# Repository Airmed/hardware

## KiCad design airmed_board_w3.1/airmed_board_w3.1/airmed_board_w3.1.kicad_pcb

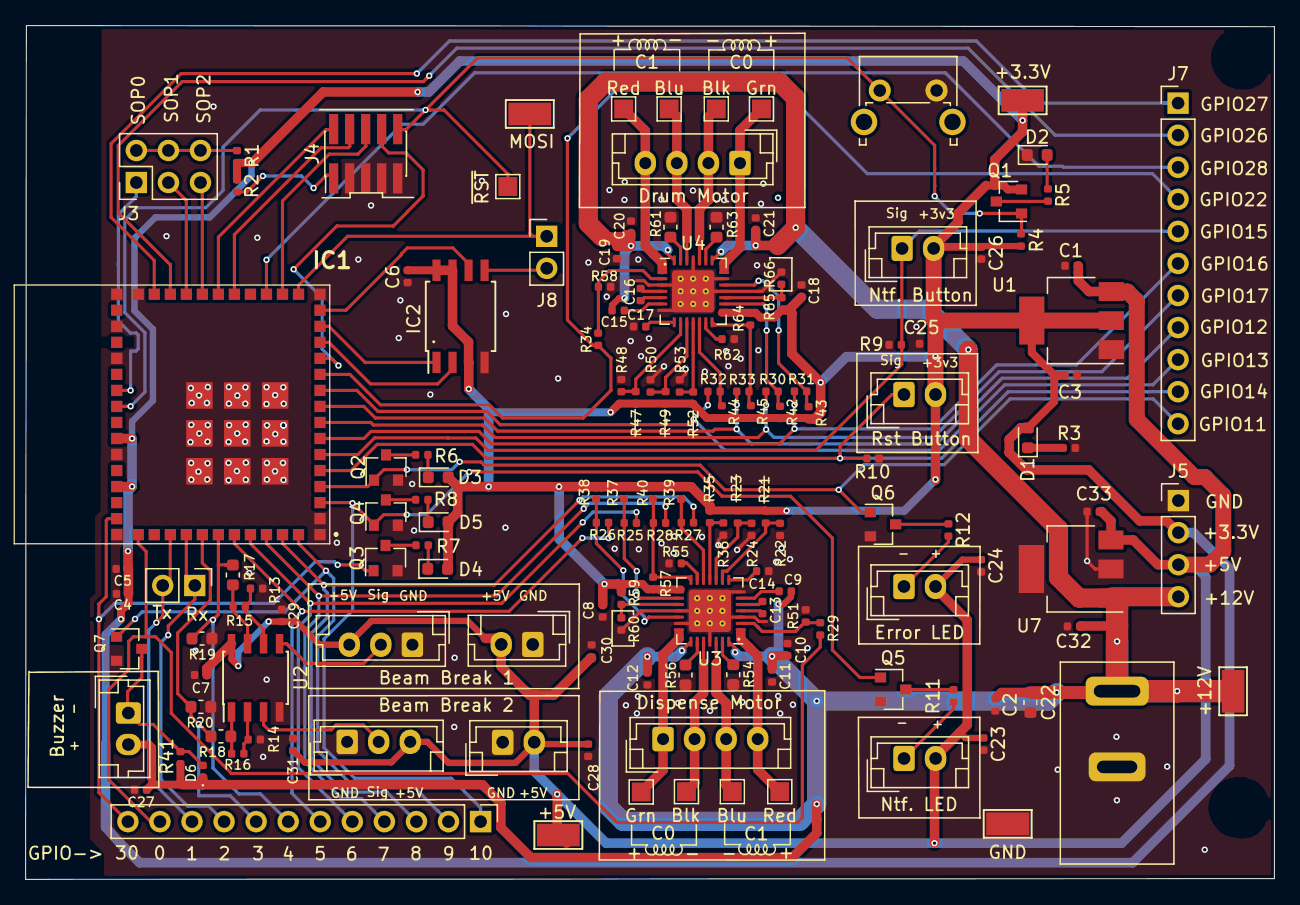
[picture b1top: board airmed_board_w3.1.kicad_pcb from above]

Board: 2 copper layers, 98.9 x 67.6 mm, 151 parts (0 on the bottom side), 102 nets.

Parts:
+3.3V, +5V, +12V: TestPoint_Flag; TestPoint_Keystone_5015_Micro-Minature
Blk: TestPoint_Flag; TestPoint_Pad_1.5x1.5mm
Blk#2: TestPoint_Flag; TestPoint_Pad_1.5x1.5mm
Blu: TestPoint_Flag; TestPoint_Pad_1.5x1.5mm
Blu#2: TestPoint_Flag; TestPoint_Pad_1.5x1.5mm
C1, C3, C10, C19: 4.7uF; C_0402_1005Metric
C2: 1uF; C_0402_1005Metric
C4, C5, C6, C7, C9, C11, C12, C13, C15, C16, C20, C21, C23, C24, C25, C26, C27, C28, C29, C30, C31, C33: 0.1uF; C_0402_1005Metric
C8, C14, C17, C18, C32: 0.22uF; C_0402_1005Metric
C22: 10uF; C_0603_1608Metric
D1, D2, D3, D4, D5: LED; LED_0603_1608Metric
D6: 350mV; D_0402_1005Metric
GND: TestPoint_Flag; TestPoint_Keystone_5015_Micro-Minature
Grn: TestPoint_Flag; TestPoint_Pad_1.5x1.5mm
Grn#2: TestPoint_Flag; TestPoint_Pad_1.5x1.5mm
IC1: CC3220MODASF12MONR; CC3220MODASM2MONR
IC2: MX25R3235FM1IL0; SOIJ-8_5.3x5.3mm_P1.27mm
J1, J8: Conn_01x02_Male; PinHeader_1x02_P2.54mm_Vertical
J2: Barrel_Jack; BarrelJack_CUI_PJ-037A_Horizontal
J3: Conn_02x03_Odd_Even; PinHeader_2x03_P2.54mm_Vertical
J4: Conn_02x05_Odd_Even; PinHeader_2x05_P1.27mm_Vertical_SMD
J5: Conn_01x04_Male; PinHeader_1x04_P2.54mm_Vertical
J6: Conn_01x12_Male; PinHeader_1x12_P2.54mm_Vertical
J7: Conn_01x11_Male; PinHeader_1x11_P2.54mm_Vertical
J9, J10, J11, J12, J13, J15, J17: Conn_01x02_Male; JST_EH_B02B-EH-A_1x02_P2.50mm_Vertical
J14, J16: Conn_01x03_Male; JST_EH_B03B-EH-A_1x03_P2.50mm_Vertical
J18, J19: Conn_01x04_Female; JST_EH_B04B-EH-A_1x04_P2.50mm_Vertical
MOSI: TestPoint_Flag; TestPoint_Keystone_5015_Micro-Minature
Q1: Q_PMOS_GSD; SOT-23
Q2, Q3, Q4, Q5, Q6, Q7: Q_NMOS_GSD; SOT-23
R1: 270; R_0402_1005Metric
R2, R4, R9, R10, R13, R14, R41: 1K; R_0402_1005Metric
R3, R5, R6, R7, R8: 68; R_0402_1005Metric
R11, R12: 100; R_0402_1005Metric
R15, R16, R60, R66: 18K; R_0402_1005Metric
R17, R18: 680; R_0603_1608Metric
R19, R20: 330; R_0603_1608Metric
R21, R23, R25, R26, R27, R28, R29, R30, R31, R32, R33, R34, R35, R47, R49, R52: 0; R_0402_1005Metric
R22, R24, R36, R37, R38, R39, R40, R42, R43, R44, R45, R48, R50, R53, R59, R65: 20K; R_0402_1005Metric
R51, R57, R58, R64: 100K; R_0402_1005Metric
R54, R56, R61, R63: 0.2; R_0603_1608Metric
R55, R62: 10K; R_0402_1005Metric
Red: TestPoint_Flag; TestPoint_Pad_1.5x1.5mm
Red#2: TestPoint_Flag; TestPoint_Pad_1.5x1.5mm
SW1: SW_Push; SW_Tactile_SPST_Angled_PTS645Vx39-2LFS
U1: AP2114; SOT-223-3_TabPin2
U2: TLC272; SOIC-8_3.9x4.9mm_P1.27mm
U3, U4: A4988; QFN-28-1EP_5x5mm_P0.5mm_EP3.35x3.35mm_ThermalVias
U7: LM340; SOT-223-3_TabPin2

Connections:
+3V3: +3.3V.1, C3.1, C4.1, C5.1, C6.1, C8.2, C18.2, C25.1, C26.1, D1.2, D3.2, D4.2, D5.2, IC1.37, IC1.40, IC2.3, IC2.7, IC2.8, J5.2, J9.2, J10.2, Q1.2, R1.1, R2.1, R4.1, R21.2, R23.2, R35.2, R37.2, R38.2, R39.2, R40.2, R42.2, R43.2, R44.2, R45.2, R47.2, R49.2, R52.2, R57.1, R59.2, R64.1, R65.2, U1.2, U3.15, U4.15
+5V: +5V.1, C1.1, C7.1, C23.1, C24.1, C28.1, C29.1, C30.1, C31.1, C33.1, J5.3, J11.2, J12.2, J13.2, J14.3, J15.2, J16.3, U1.3, U2.8, U7.3
+12V: +12V.1, C2.1, C9.1, C10.1, C11.1, C12.1, C15.1, C19.1, C20.1, C21.1, C22.1, C27.1, C32.1, D6.1, J2.1, J5.4, J17.2, R41.1, U3.22, U3.28, U4.22, U4.28, U7.1
BBSense1: IC1.49, J6.7, R17.1, R19.1
BBSense2: IC1.48, J6.8, R18.1, R20.1
BuzzCtrl: IC1.54, J6.2, Q7.1
D2_DIR: R31.1, R43.1, U4.19
D2_MS1: R47.1, R48.1, U4.9
D2_MS2: R49.1, R50.1, U4.10
D2_MS3: R52.1, R53.1, U4.11
D2_OUT1A: Blk#2.1, J18.2, U4.24
D2_OUT1B: Grn#2.1, J18.1, U4.21
D2_OUT2A: Blu#2.1, J18.3, U4.26
D2_OUT2B: J18.4, Red#2.1, U4.1
D2_STEP: R30.1, R42.1, U4.16
DIR: R26.1, R38.1, U3.19
Err_LED: IC1.4, J7.11, Q2.1, Q6.1
FLASH_CLK: IC1.15, IC2.6
FLASH_MISO: IC1.13, IC2.2
FLASH_MOSI: IC1.17, J8.1, MOSI.1
FLASH_nCS: IC1.14, IC2.1
GND: C1.2, C2.2, C3.2, C4.2, C5.2, C6.2, C7.2, C8.1, C10.2, C11.2, C12.2, C14.2, C17.2, C18.1, C19.2, C20.2, C21.2, C22.2, C23.2, C24.2, C25.2, C26.2, C27.2, C28.2, C29.2, C30.2, C31.2, C32.2, C33.2, D2.1, GND.1, IC1.1, IC1.2, IC1.16, IC1.27, IC1.28, IC1.30, IC1.32, IC1.38, IC1.43, IC1.55, IC1.56, IC1.57, IC1.58, IC1.59, IC1.60, IC1.61, IC1.62, IC1.63, IC2.4, J2.2, J4.3, J4.5, J4.7, J4.9, J5.1, J13.1, J14.1, J15.1, J16.1, Q2.2, Q3.2, Q4.2, Q5.2, Q6.2, Q7.2, R3.2, R9.1, R10.1, R13.2, R14.2, R19.2, R20.2, R22.2, R24.2, R36.2, R48.2, R50.2, R51.2, R53.2, R54.2, R55.2, R56.1, R58.2, R60.2, R61.2, R62.2, R63.1, R66.2, SW1.2, U1.1, U2.4, U3.3, U3.7, U3.18, U3.20, U3.25, U3.29, U4.3, U4.7, U4.18, U4.20, U4.25, U4.29, U7.2
GPIO0: IC1.44, J6.11, R29.2
GPIO1: IC1.46, J1.2, J6.10
GPIO2: IC1.47, J1.1, J6.9
GPIO5: IC1.50, J6.6, R26.2
GPIO6: IC1.51, J6.5, R25.2
GPIO7: IC1.52, J6.4, R28.2
GPIO8: IC1.53, J6.3, R27.2
GPIO10: IC1.3, J6.1, Q4.1, Q5.1
GPIO12: IC1.9, J7.8, R33.2
GPIO13: IC1.10, J7.9, R32.2
GPIO14: IC1.5, J7.10, J10.1, R10.2
GPIO15: IC1.6, J7.5, J9.1, R9.2
GPIO16: IC1.7, J7.6, R31.2
GPIO17: IC1.8, J7.7, R30.2
GPIO22: IC1.11, J7.4, R34.2
GPIO26: IC1.25, J7.2
GPIO27: IC1.26, J7.1
GPIO28: IC1.19, J7.3
GPIO30: IC1.42, J6.12, Q3.1
JTAG_TCK: IC1.21, J4.4
JTAG_TDI: IC1.12, J4.8
JTAG_TDO: IC1.18, J4.6
JTAG_TMS: IC1.22, J4.2
MS1: R21.1, R22.1, U3.9
MS2: R23.1, R24.1, U3.10
MS3: R35.1, R36.1, U3.11
unnamed: C9.2, U3.6
unnamed: C13.1, U3.5
unnamed: C13.2, U3.4
unnamed: C14.1, U3.8
unnamed: C15.2, U4.6
unnamed: C16.1, U4.5
unnamed: C16.2, U4.4
unnamed: C17.1, U4.8
unnamed: D1.1, R3.1
unnamed: D2.2, R5.1
unnamed: D3.1, R6.1
unnamed: D4.1, R7.1
unnamed: D5.1, R8.1
unnamed: D6.2, J17.1, Q7.3, R41.2
unnamed: IC2.5, J8.2
unnamed: J3.2, J3.4, J3.6, R1.2
unnamed: J4.1, R2.2
unnamed: J11.1, R11.2
unnamed: J12.1, R12.2
unnamed: J14.2, U2.5
unnamed: J16.2, U2.3
unnamed: Q1.3, R5.2
unnamed: Q2.3, R6.2
unnamed: Q3.3, R7.2
unnamed: Q4.3, R8.2
unnamed: Q5.3, R11.1
unnamed: Q6.3, R12.1
unnamed: R13.1, R15.1, U2.6
unnamed: R14.1, R16.1, U2.2
unnamed: R15.2, R17.2, U2.7
unnamed: R16.2, R18.2, U2.1
unnamed: R54.1, U3.27
unnamed: R55.1, U3.13
unnamed: R56.2, U3.23
unnamed: R59.1, R60.1, U3.17
unnamed: R61.1, U4.27
unnamed: R62.1, U4.13
unnamed: R63.2, U4.23
unnamed: R65.1, R66.1, U4.17
OUT1A: Blk.1, J19.2, U3.24
OUT1B: Grn.1, J19.1, U3.21
OUT2A: Blu.1, J19.3, U3.26
OUT2B: J19.4, Red.1, U3.1
SOP0: IC1.34, J3.1
SOP1: IC1.24, J3.3
SOP2: IC1.23, J3.5
STEP: R25.1, R37.1, U3.16
nRESET: IC1.35, J4.10, Q1.1, R4.2, SW1.1
~D2_ENABLE: R34.1, R58.1, U4.2
~D2_RESET: R32.1, R44.1, U4.12
~D2_SLEEP: R33.1, R45.1, R64.2, U4.14
~ENABLE: R29.1, R51.1, U3.2
~RESET: R27.1, R39.1, U3.12
~SLEEP: R28.1, R40.1, R57.2, U3.14

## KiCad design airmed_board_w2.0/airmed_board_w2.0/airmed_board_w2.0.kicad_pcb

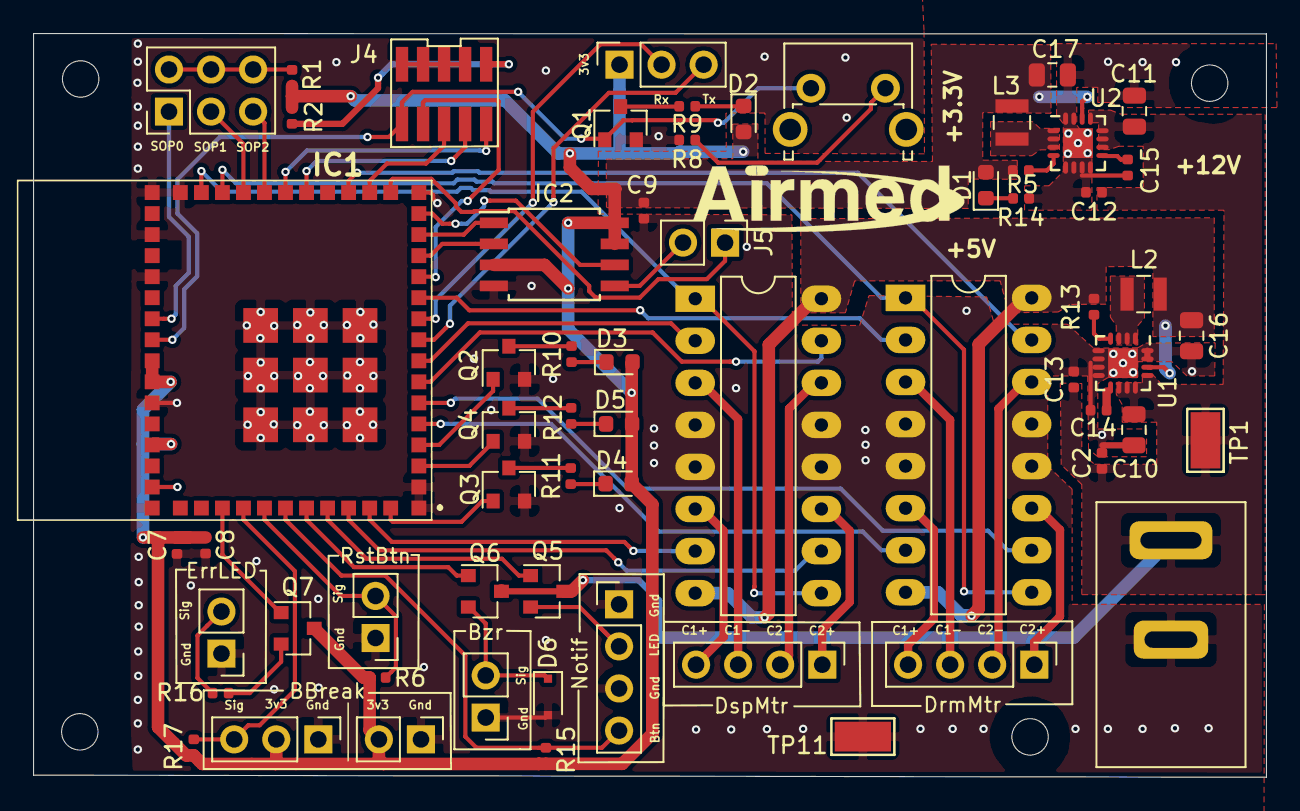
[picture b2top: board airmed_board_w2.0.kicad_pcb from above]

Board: 2 copper layers, 74.4 x 44.9 mm, 63 parts (0 on the bottom side), 68 nets.

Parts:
C2: 1uF; C_0402_1005Metric
C7, C8, C9, C12, C13: 0.1uF; C_0402_1005Metric
C10, C11: 10uF; C_0805_2012Metric
C14, C15: 3.3nF; C_0402_1005Metric
C16, C17: 22uF; C_0805_2012Metric
D1, D2, D3, D4, D5: LED; LED_0603_1608Metric
D6: 1N4148; D_SOD-323F
IC1: CC3220MODASF12MONR; CC3220MODASM2MONR
IC2: MX25R3235FM1IL0; SOIJ-8_5.3x5.3mm_P1.27mm
J1: Conn_01x03_Male; PinSocket_1x03_P2.54mm_Vertical
J2: Barrel_Jack; BarrelJack_CUI_PJ-037A_Horizontal
J3: Conn_02x03_Odd_Even; PinHeader_2x03_P2.54mm_Vertical
J4: Conn_02x05_Odd_Even; PinSocket_2x05_P1.27mm_Vertical_SMD
J5, J7, J8, J10, J11: Conn_01x02_Male; PinHeader_1x02_P2.54mm_Vertical
J9: Conn_01x04_Male; PinHeader_1x04_P2.54mm_Vertical
J12: Conn_01x03_Male; PinHeader_1x03_P2.54mm_Vertical
L2, L3: 2.2uH; L_1008_2520Metric
M1, M2: Stepper_Motor_bipolar; PinHeader_1x04_P2.54mm_Vertical
Q1, Q2, Q3, Q4, Q5, Q6, Q7: Q_NMOS_GSD; SOT-23
R1: 270; R_0402_1005Metric
R2, R6, R15, R17: 1K; R_0402_1005Metric
R5, R9, R10, R11, R12: 68; R_0402_1005Metric
R8, R16: 100; R_0402_1005Metric
R13, R14: 100K; R_0402_1005Metric
SW1: SW_Push; SW_Tactile_SPST_Angled_PTS645Vx39-2LFS
TP1, TP11: TestPoint_Flag; TestPoint_Keystone_5015_Micro-Minature
U1: TPS62133; QFN-16-1EP_3x3mm_P0.5mm_EP1.8x1.8mm
U2: TPS62132; QFN-16-1EP_3x3mm_P0.5mm_EP1.8x1.8mm
U3, U4: sn754410; DIP-16_W7.62mm_LongPads

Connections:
+3V3: C7.1, C8.1, C9.1, C17.1, D1.2, D2.2, D3.2, D4.2, D5.2, IC1.36, IC1.37, IC1.40, IC2.3, IC2.7, IC2.8, J1.1, J11.2, J12.2, L3.2, Q7.3, R1.1, R2.1, R6.2, R14.1, R15.2, R17.2, U2.14
+5V: C16.1, L2.2, R13.1, U1.14, U3.8, U3.16, U4.8, U4.16
+12V: C2.1, C10.1, C11.1, C12.1, C13.1, J2.1, Q5.3, Q6.3, TP1.1, U1.10, U1.11, U1.12, U1.13, U2.10, U2.11, U2.12, U2.13
/FLASH_CLK: IC1.15, IC2.6
/FLASH_MISO: IC1.13, IC2.2
/FLASH_MOSI: IC1.17, J5.1
/FLASH_nCS: IC1.14, IC2.1
/GPIO1: IC1.46, Q7.1
/GPIO2: IC1.47, J12.3, R17.1
/GPIO3: IC1.48, J8.2, R6.1
/GPIO4: IC1.49, J9.4, R15.1
/GPIO5: IC1.50, Q6.1
/GPIO6: IC1.51, Q5.1
/GPIO7: IC1.52, U4.10
/GPIO8: IC1.53, U4.7
/GPIO9: IC1.54, Q3.1
/GPIO10: IC1.3, Q4.1
/GPIO11: IC1.4, Q2.1
/GPIO12: IC1.9, J1.3
/GPIO13: IC1.10, J1.2
/GPIO14: IC1.5, U3.7
/GPIO15: IC1.6, U3.10
/GPIO16: IC1.7, U4.15
/GPIO17: IC1.8, U4.2
/GPIO22: IC1.11, U3.2
/GPIO26: IC1.25, U3.1, U3.9
/GPIO27: IC1.26, U4.1, U4.9
/GPIO28: IC1.19, U3.15
/JTAG_TCK: IC1.21, J4.4
/JTAG_TDI: IC1.12, J4.8
/JTAG_TDO: IC1.18, J4.6
/JTAG_TMS: IC1.22, J4.2
/SOP0: IC1.34, J3.1
/SOP1: IC1.24, J3.3
/SOP2: IC1.23, J3.5
/nRESET: IC1.35, J4.10, Q1.1, SW1.1
GND: C2.2, C7.2, C8.2, C9.2, C10.2, C11.2, C12.2, C13.2, C14.2, C15.2, C16.2, C17.2, D6.2, IC1.1, IC1.2, IC1.16, IC1.27, IC1.28, IC1.30, IC1.32, IC1.38, IC1.43, IC1.55, IC1.56, IC1.57, IC1.58, IC1.59, IC1.60, IC1.61, IC1.62, IC1.63, IC2.4, J2.2, J4.3, J4.5, J4.7, J4.9, J7.1, J8.1, J9.1, J9.3, J10.1, J11.1, J12.1, Q1.2, Q2.2, Q3.2, Q4.2, R5.2, R8.2, TP11.1, U1.5, U1.6, U1.7, U1.8, U1.15, U1.16, U1.17, U2.5, U2.6, U2.7, U2.8, U2.15, U2.16, U2.17, U3.4, U3.5, U3.12, U3.13, U4.4, U4.5, U4.12, U4.13
unnamed: C14.1, U1.9
unnamed: C15.1, U2.9
unnamed: D1.1, R5.1
unnamed: D2.1, R9.1
unnamed: D3.1, R10.1
unnamed: D4.1, R11.1
unnamed: D5.1, R12.1
unnamed: D6.1, J7.2, Q6.2
unnamed: IC2.5, J5.2
unnamed: J3.2, J3.4, J3.6, R1.2
unnamed: J4.1, R2.2
unnamed: J9.2, Q5.2
unnamed: J10.2, R16.2
unnamed: L2.1, U1.1, U1.2, U1.3
unnamed: L3.1, U2.1, U2.2, U2.3
unnamed: M1.1, U3.11
unnamed: M1.2, U3.14
unnamed: M1.3, U3.3
unnamed: M1.4, U3.6
unnamed: M2.1, U4.11
unnamed: M2.2, U4.14
unnamed: M2.3, U4.3
unnamed: M2.4, U4.6
unnamed: Q1.3, R9.2
unnamed: Q2.3, R10.2
unnamed: Q3.3, R11.2
unnamed: Q4.3, R12.2
unnamed: Q7.2, R16.1
unnamed: R8.1, SW1.2
unnamed: R13.2, U1.4
unnamed: R14.2, U2.4

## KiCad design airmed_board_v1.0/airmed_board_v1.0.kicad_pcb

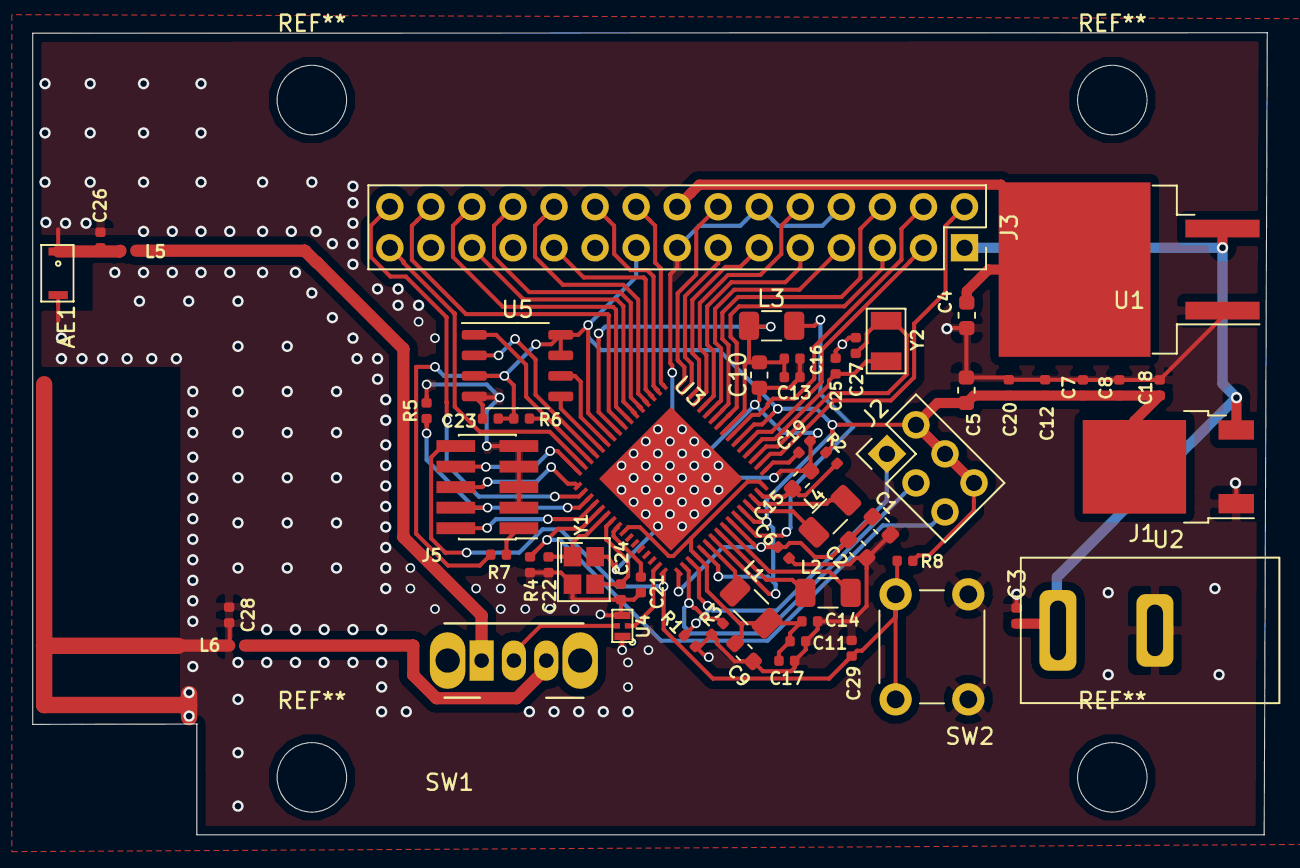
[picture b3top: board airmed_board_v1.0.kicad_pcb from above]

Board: 2 copper layers, 76.4 x 49.6 mm, 57 parts (0 on the bottom side), 58 nets.

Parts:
AE1: Antenna_Shield; AH316M
C1, C2: 22uF; C_0603_1608Metric
C3, C11, C13, C14, C16, C17, C18, C19, C20, C21, C23: 0.1uF; C_0402_1005Metric
C4, C5, C9, C10, C15: 10uF; C_0603_1608Metric
C6, C29: 1uF; C_0402_1005Metric
C7, C8, C12: 4.7uF; C_0402_1005Metric
C22, C24: 6.2p; C_0402_1005Metric
C25, C27: 10p; C_0402_1005Metric
C26, C28: 0.5p; C_0402_1005Metric
J1: Barrel_Jack; BarrelJack_CUI_PJ-037A_Horizontal
J2: Conn_02x03_Odd_Even; PinHeader_2x03_P2.54mm_Vertical
J3: Conn_02x15_Top_Bottom; PinSocket_2x15_P2.54mm_Vertical
J5: Conn_02x05_Odd_Even; PinHeader_2x05_P1.27mm_Vertical_SMD
L1, L3: 2.2uH; L_1206_3216Metric
L2: 1uH; L_1206_3216Metric
L4: 10uH; L_1206_3216Metric
L5, L6: 3.3nH; L_0402_1005Metric
R1, R3, R5: 100k; R_0402_1005Metric
R2: 0; R_0402_1005Metric
R4: 2.7k; R_0402_1005Metric
R6: 100K; R_0402_1005Metric
R7: 1K; R_0402_1005Metric
R8: 10k; R_0402_1005Metric
SW1: SW_SPDT; SW_CuK_OS102011MA1QN1_SPDT_Angled
SW2: SW_Push; SW_PUSH_6mm_H4.3mm
U1: AP1084K50L-13; TO-263-2
U2: AZ1084CD-3.3TRG1; TO-252-2
U3: CC3220
U4: DEA202450BT-1294C1-H; TDKFilter1294C1H
U5: MX25R3235F; SSOP-8_3.9x5.05mm_P1.27mm
Y1: Crystal_GND24; Crystal_SMD_Epson_FA-20H-4pin_2.5mm_2.0mm
Y2: Crystal; Crystal_SMD_Abracon_ABS07-2Pin_3.2mm_1.5mm

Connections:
+3V3: C5.1, C7.1, C8.1, C12.1, C18.1, C20.1, C23.1, J2.2, J2.4, J2.6, J3.17, R2.2, R6.1, R7.2, R8.2, U2.2, U3.10, U3.37, U3.39, U3.44, U3.54, U5.3, U5.7, U5.8
+5V: C4.1, J3.16, U1.2
+12V: C3.1, J1.1, J3.1, U1.3, U2.3
/GPIO0: J3.2, U3.50
/GPIO1: J3.4, U3.55
/GPIO2: J3.5, U3.57
/GPIO3: J3.6, U3.58
/GPIO4: J3.7, U3.59
/GPIO5: J3.9, U3.60
/GPIO6: J3.10, U3.61
/GPIO7: J3.11, U3.62
/GPIO8: J3.13, U3.63
/GPIO9: J3.14, U3.64
/GPIO10: J3.18, U3.1
/GPIO11: J3.20, U3.2
/GPIO12: J3.21, U3.3
/GPIO13: J3.22, U3.4
/GPIO14: J3.24, U3.5
/GPIO15: J3.25, U3.6
/GPIO16: J3.26, U3.7
/GPIO17: J3.28, U3.8
/GPIO22: J3.29, U3.15
/GPIO28: J3.30, U3.18
/GPIO30: J3.3, U3.53
/RTC_XTAL_N: C25.1, U3.52, Y2.1
/RTC_XTAL_P: C27.1, U3.51, Y2.2
/TCK: J5.4, R5.1, U3.19
/TDI: J5.8, U3.16
/TDO: J5.6, U3.17
/TMS: J5.2, U3.20
/WLAN_XTAL_N: C22.1, U3.22, Y1.1
/WLAN_XTAL_P: C24.1, U3.23, Y1.3
/nRESET: C29.1, J5.10, R8.1, SW2.1, U3.32
GND: AE1.1, AE1.2, C1.2, C2.2, C3.2, C4.2, C5.2, C6.2, C7.2, C8.2, C9.2, C10.2, C11.2, C12.2, C13.2, C14.2, C15.2, C16.2, C17.2, C18.2, C19.2, C20.2, C21.2, C22.2, C23.2, C24.2, C25.2, C26.1, C26.2, C27.2, C28.1, C28.2, C29.2, J1.2, J3.8, J3.12, J3.15, J3.19, J3.23, J3.27, J5.3, J5.5, J5.7, J5.9, L5.2, L6.2, R1.2, R3.2, R4.2, R5.2, SW2.2, U1.1, U2.1, U3.65, U4.2, U4.4, U5.4, Y1.2, Y1.4
unnamed: C1.1, C2.1, C6.1, U3.33, U3.42
unnamed: C10.1, C13.1, C16.1, L3.1, U3.9, U3.56
unnamed: C9.1, C11.1, C14.1, C17.1, L1.1, U3.25, U3.36, U3.48
unnamed: C15.1, R2.1, U3.47
unnamed: C19.1, U3.49
unnamed: C21.1, U3.24
unnamed: J2.1, R1.1, U3.35
unnamed: J2.3, R3.1, U3.34
unnamed: J2.5, R4.1, U3.21
unnamed: J5.1, R7.1
unnamed: L1.2, U3.38
unnamed: L2.1, U3.41
unnamed: L2.2, U3.40
unnamed: L3.2, U3.43
unnamed: L4.1, U3.46
unnamed: L4.2, U3.45
unnamed: L5.1, SW1.1
unnamed: L6.1, SW1.3
unnamed: R6.2, U3.14, U5.1
unnamed: SW1.2, U4.3
unnamed: U3.11, U5.6
unnamed: U3.12, U5.5
unnamed: U3.13, U5.2
unnamed: U3.31, U4.1

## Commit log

2018-10-11 initial commit, added fancy README and Airmed assets
2018-10-11 fixed fancy README
2018-10-16 created project for schematics
2018-10-18 first draft of circuit schematic
2018-10-31 Board Schematic v1.0 updated
2018-11-29 board
2019-01-22 added so many things
2019-01-22 sorted old gerber
2019-02-19 added literally everything
2019-04-30 literally all the board designs. Like this is it. THis is what it takes.
